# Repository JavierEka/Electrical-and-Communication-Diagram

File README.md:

# Electrical and Communication Diagram

## Fuel Engine Remote Control (FERC)

### Electrical Diagram

### Communication Diagram

### Deskripsi
Diagram ini menunjukkan sistem Engine Remote Control (ERC) berbasis STM32, didukung baterai utama 25,2V yang dialirkan melalui regulator (buck boost) untuk kebutuhan tegangan 12V, 7,4V, dan 5V. Komponen seperti GPS, kamera, servo, ESC, dan thruster terhubung melalui STM32 untuk pengontrolan. Sistem komunikasi melibatkan LoRa dan CANBUS, sementara receiver menghubungkan transmitter dengan servo. Baterai cadangan 16,8V mendukung PCB darurat dan motor ESC. Regulator UBEC memastikan pasokan aman ke perangkat seperti lampu dan PC mini. Diagram menekankan alur energi dan sinyal untuk mengoperasikan sistem dengan efisien.

## Electrical Remote Control (ERC)

### Electrical Diagram

### Communication Diagram

### Deskripsi
Diagram Fuel Engine Remote Control (FERC) ini menunjukkan pengendalian jarak jauh sistem mesin berbahan bakar yang terintegrasi. Baterai utama Li-Po 25,2V mengalirkan daya melalui regulator buck boost untuk menyediakan tegangan 12V, 7,4V, dan 5V ke berbagai komponen. Mikrokontroler STM32 berperan sebagai pusat kendali, menerima sinyal dari modul LoRa untuk mengontrol penginjeksian bahan bakar, pengoperasian mesin, dan propeller melalui ESC. Servo digunakan untuk manuver, dan fitur keselamatan berupa PCB darurat siap memutus daya jika terjadi kegagalan. Komunikasi dilakukan melalui receiver yang menerima input dari transmitter, sedangkan Mini PC, GPS, dan kamera mendukung fungsi tambahan untuk monitoring dan navigasi.

# Contoh Program Untuk Mengecek Jurusan
File Untuk Programnya ada di [link ini](Cek_Jurusan.cpp)

    #include <stdio.h>
    #include <string.h>
    #include <stdlib.h>
    
    typedef struct {
        char nama[50];
        char nrp[15];
        char jurusan[50];
    } Mahasiswa;
    
    int cek_nama_sama(Mahasiswa data_mahasiswa[], int jumlah, const char *nama) {
        for (int i = 0; i < jumlah; i++) {
            if (strcmp(data_mahasiswa[i].nama, nama) == 0) {
                return 1;
            }
        }
        return 0;
    }
    
    int cek_nrp_sama(Mahasiswa data_mahasiswa[], int jumlah, const char *nrp) {
        for (int i = 0; i < jumlah; i++) {
            if (strcmp(data_mahasiswa[i].nrp, nrp) == 0) {
                return 1;
            }
        }
        return 0;
    }
    
    int validasi_nrp(const char *nrp) {
        if (strlen(nrp) != 10) {
            return 0; 
        }
        char dua_digit[3];
        strncpy(dua_digit, nrp, 2);
        dua_digit[2] = '\0';
        int angka = atoi(dua_digit); 
        return (angka == 20 || angka == 50); 
    }
    
    void cari_kelompok(Mahasiswa data_mahasiswa[], int jumlah) {
        int sudah_diproses[5] = {0};
    
        for (int i = 0; i < jumlah; i++) {
            if (sudah_diproses[i]) {
                continue; 
            }
    
            char nrp_awal[5];
            strncpy(nrp_awal, data_mahasiswa[i].nrp, 4);
            nrp_awal[4] = '\0';
    
            int count = 0;
    
            for (int j = 0; j < jumlah; j++) {
                if (!sudah_diproses[j] && strncmp(data_mahasiswa[j].nrp, nrp_awal, 4) == 0) {
                    count++;
                }
            }
    
            if (count > 1) {
                printf("\nMahasiswa dengan jurusan yang sama : ");
    
                for (int j = 0; j < jumlah; j++) {
                    if (!sudah_diproses[j] && strncmp(data_mahasiswa[j].nrp, nrp_awal, 4) == 0) {
                        printf("%s ", data_mahasiswa[j].nama);
                        sudah_diproses[j] = 1; 
                    }
                }
            }
        }
    }
    
    int main() {
        Mahasiswa data_mahasiswa[5];
        int jumlah = 0;
    
        printf("Masukkan data mahasiswa (maksimum %d mahasiswa):\n", 5);
    
        while (jumlah < 5) {
            Mahasiswa mhs;
    
            printf("\nNama: ");
            scanf(" %[^\n]s", mhs.nama);
    
            if (cek_nama_sama(data_mahasiswa, jumlah, mhs.nama)) {
                printf("Nama '%s' sudah ada!\n", mhs.nama);
                continue;
            }
    
            printf("NRP: ");
            scanf(" %s", mhs.nrp);
    
            if (cek_nrp_sama(data_mahasiswa, jumlah, mhs.nrp)) {
                printf("NRP '%s' sudah ada!\n", mhs.nrp);
                continue;
            }
    
            if (!validasi_nrp(mhs.nrp)) {
                printf("NRP Tidak Valid!\n");
                continue;
            }
    
            printf("Jurusan: ");
            scanf(" %[^\n]s", mhs.jurusan);
    
            data_mahasiswa[jumlah] = mhs;
            jumlah++;
        }
    
        cari_kelompok(data_mahasiswa, jumlah);
    
        return 0;
    }

# Penugasan PCB
File KiCad dari PCB dapat diakses dengan [link ini](Boost%20Converter)

## Schematics

## PCB

## 3D

Saya melakukan revisi di bagian PCB, dimana saya arrange ulang untuk menciptakan ground plane yang ideal.

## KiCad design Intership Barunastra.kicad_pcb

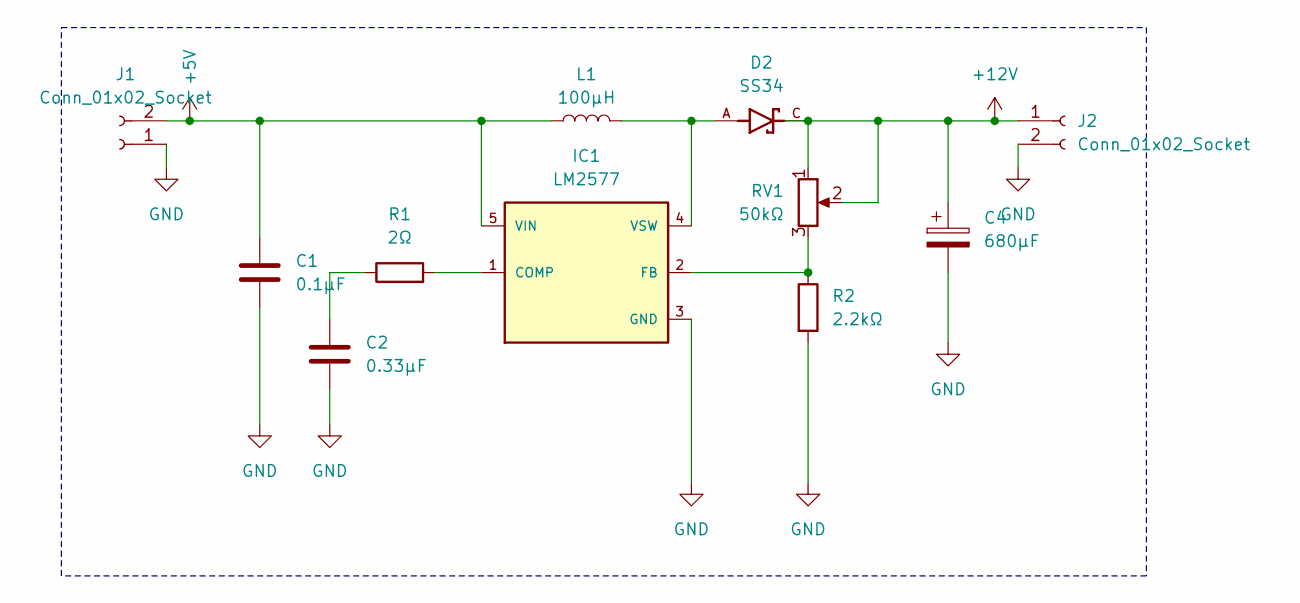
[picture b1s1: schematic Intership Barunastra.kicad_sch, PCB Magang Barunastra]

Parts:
C1: 0.1µF; CAP_EEEFK1C101V
C2: 0.33µF; CAP_EEEFK1C101V
C4: 680µF; CAP_EEEFK1C101V
D2: SS34; DIO_SS34; PARTREV S2311
IC1: LM2577
J1, J2: Conn_01x02_Socket; PhoenixContact_GMSTBA_2,5_2-G-7,62_1x02_P7.62mm_Horizontal
L1: 100µH; INDP125125X600N
R1: 2Ω; R_1206_3216Metric_Pad1.30x1.75mm_HandSolder
R2: 2.2kΩ; R_1206_3216Metric_Pad1.30x1.75mm_HandSolder
RV1: 50kΩ; Potentiometer_Bourns_3299W_Vertical

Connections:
+5V: C1.1, IC1.5 (VIN), J1.2, L1.1
+12V: C4.1, D2.C, J2.1, RV1.1, RV1.2
GND: C1.2, C2.2, C4.2, IC1.3 (GND), J1.1, J2.2, R2.2
unnamed: C2.1, R1.1
unnamed: IC1.1 (COMP), R1.2
unnamed: IC1.2 (FB), R2.1, RV1.3
unnamed: D2.A, IC1.4 (VSW), L1.2

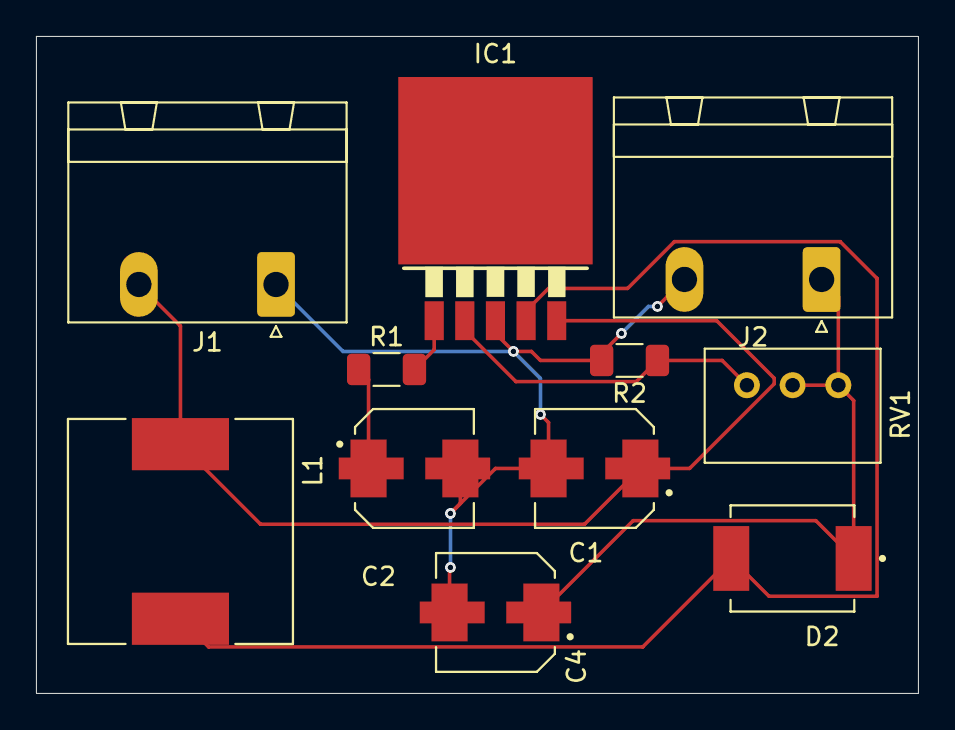
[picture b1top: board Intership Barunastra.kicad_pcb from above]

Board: 2 copper layers, 49.0 x 36.5 mm, 11 parts (0 on the bottom side), 7 nets.

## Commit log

2024-11-22 edit
2024-11-27 nambah file
2024-11-27 ubah
2024-11-27 tipedata
2024-11-30 tambah file
2024-11-30 edit file
